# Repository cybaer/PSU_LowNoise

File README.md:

PSU with very low noise (de noiser)

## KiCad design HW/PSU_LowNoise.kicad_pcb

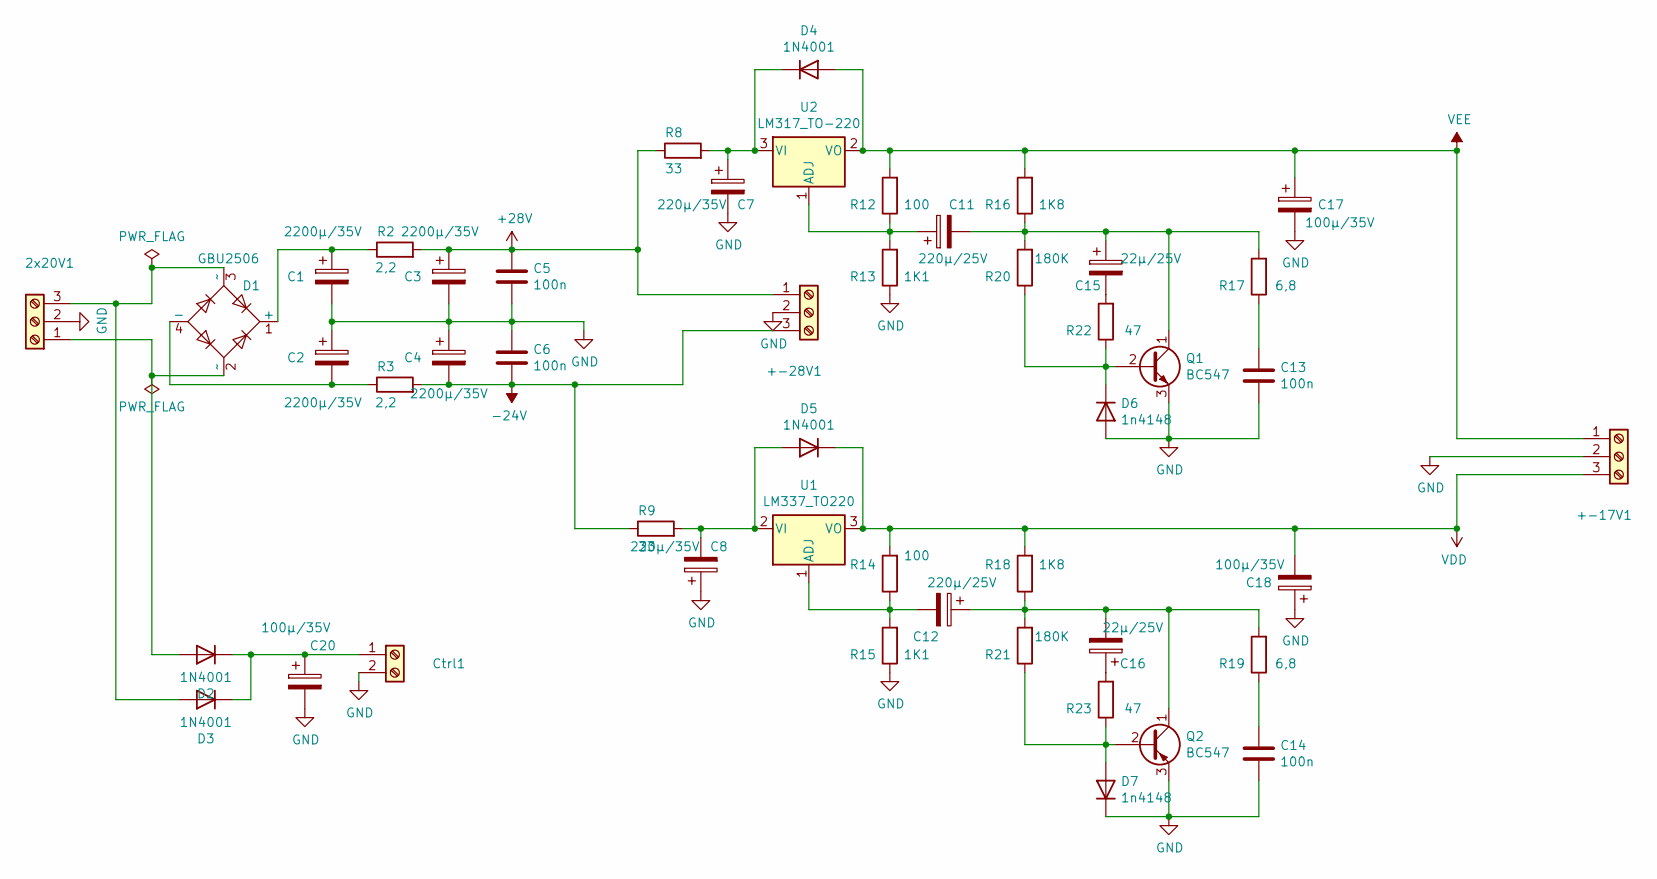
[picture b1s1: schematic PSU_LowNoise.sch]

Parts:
2x20V1: Screw_Terminal_01x03; TerminalBlock_MetzConnect_Type055_RT01503HDWU_1x03_P5.00mm_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
+-17V1, +-28V1: Screw_Terminal_01x03; TerminalBlock_MetzConnect_Type055_RT01503HDWU_1x03_P5.00mm_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
C1, C2, C3, C4: 2200µ/35V; CP_Radial_D12.5mm_P5.00mm
C5, C6, C13, C14: 100n; C_Disc_D3.4mm_W2.1mm_P2.50mm
C7, C8: 220µ/35V; CP_Radial_D8.0mm_P5.00mm
C11, C12: 220µ/25V; CP_Radial_D8.0mm_P5.00mm
C15, C16: 22µ/25V; CP_Radial_D5.0mm_P2.00mm
C17, C18, C20: 100µ/35V; CP_Radial_D8.0mm_P5.00mm
Ctrl1: Screw_Terminal_01x02; TerminalBlock_MetzConnect_Type055_RT01502HDWU_1x02_P5.00mm_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
D1: GBU2506; Diode_Bridge_Vishay_GBU
D2, D3, D4, D5: 1N4001; D_DO-41_SOD81_P10.16mm_Horizontal
D6, D7: 1n4148; D_DO-35_SOD27_P7.62mm_Horizontal
Q1, Q2: BC547; TO-92_Inline
R2, R3: 2,2; R_Axial_DIN0207_L6.3mm_D2.5mm_P7.62mm_Horizontal
R8, R9: 33; R_Axial_DIN0309_L9.0mm_D3.2mm_P12.70mm_Horizontal
R12, R14: 100; R_Axial_DIN0207_L6.3mm_D2.5mm_P7.62mm_Horizontal
R13, R15: 1K1; R_Axial_DIN0207_L6.3mm_D2.5mm_P7.62mm_Horizontal
R16, R18: 1K8; R_Axial_DIN0207_L6.3mm_D2.5mm_P7.62mm_Horizontal
R17, R19: 6,8; R_Axial_DIN0207_L6.3mm_D2.5mm_P7.62mm_Horizontal
R20, R21: 180K; R_Axial_DIN0207_L6.3mm_D2.5mm_P7.62mm_Horizontal
R22, R23: 47; R_Axial_DIN0207_L6.3mm_D2.5mm_P7.62mm_Horizontal
U1: LM337_TO220; TO-220-3_Vertical
U2: LM317_TO-220; TO-220-3_Vertical

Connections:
+28V: +-28V1.1, C3.1, C5.1, R2.2, R8.1
-24V: +-28V1.3, C4.2, C6.2, R3.2, R9.1
GND: 2x20V1.2, +-17V1.2, +-28V1.2, C1.2, C2.1, C3.2, C4.1, C5.2, C6.1, C7.2, C8.1, C13.2, C14.2, C17.2, C18.1, C20.2, Ctrl1.2, D6.2 (A), D7.1 (K), Q1.3 (E), Q2.3 (E), R13.1, R15.1
unnamed: 2x20V1.1, D1.2 (~~), D2.2 (A)
unnamed: 2x20V1.3, D1.3 (~~), D3.2 (A)
unnamed: C1.1, D1.1 (+), R2.1
unnamed: C2.2, D1.4 (-), R3.1
unnamed: C7.1, D4.1 (K), R8.2, U2.3 (VI)
unnamed: C8.2, D5.2 (A), R9.2, U1.2 (VI)
unnamed: C11.1, R12.1, R13.2, U2.1 (ADJ)
unnamed: C11.2, C15.1, Q1.1 (C), R16.1, R17.2, R20.2
unnamed: C12.1, C16.2, Q2.1 (C), R18.1, R19.2, R21.2
unnamed: C12.2, R14.1, R15.2, U1.1 (ADJ)
unnamed: C13.1, R17.1
unnamed: C14.1, R19.1
unnamed: C15.2, R22.2
unnamed: C16.1, R23.2
unnamed: C20.1, Ctrl1.1, D2.1 (K), D3.1 (K)
unnamed: D6.1 (K), Q1.2 (B), R20.1, R22.1
unnamed: D7.2 (A), Q2.2 (B), R21.1, R23.1
VDD: +-17V1.3, C18.2, D5.1 (K), R14.2, R18.2, U1.3 (VO)
VEE: +-17V1.1, C17.1, D4.2 (A), R12.2, R16.2, U2.2 (VO)

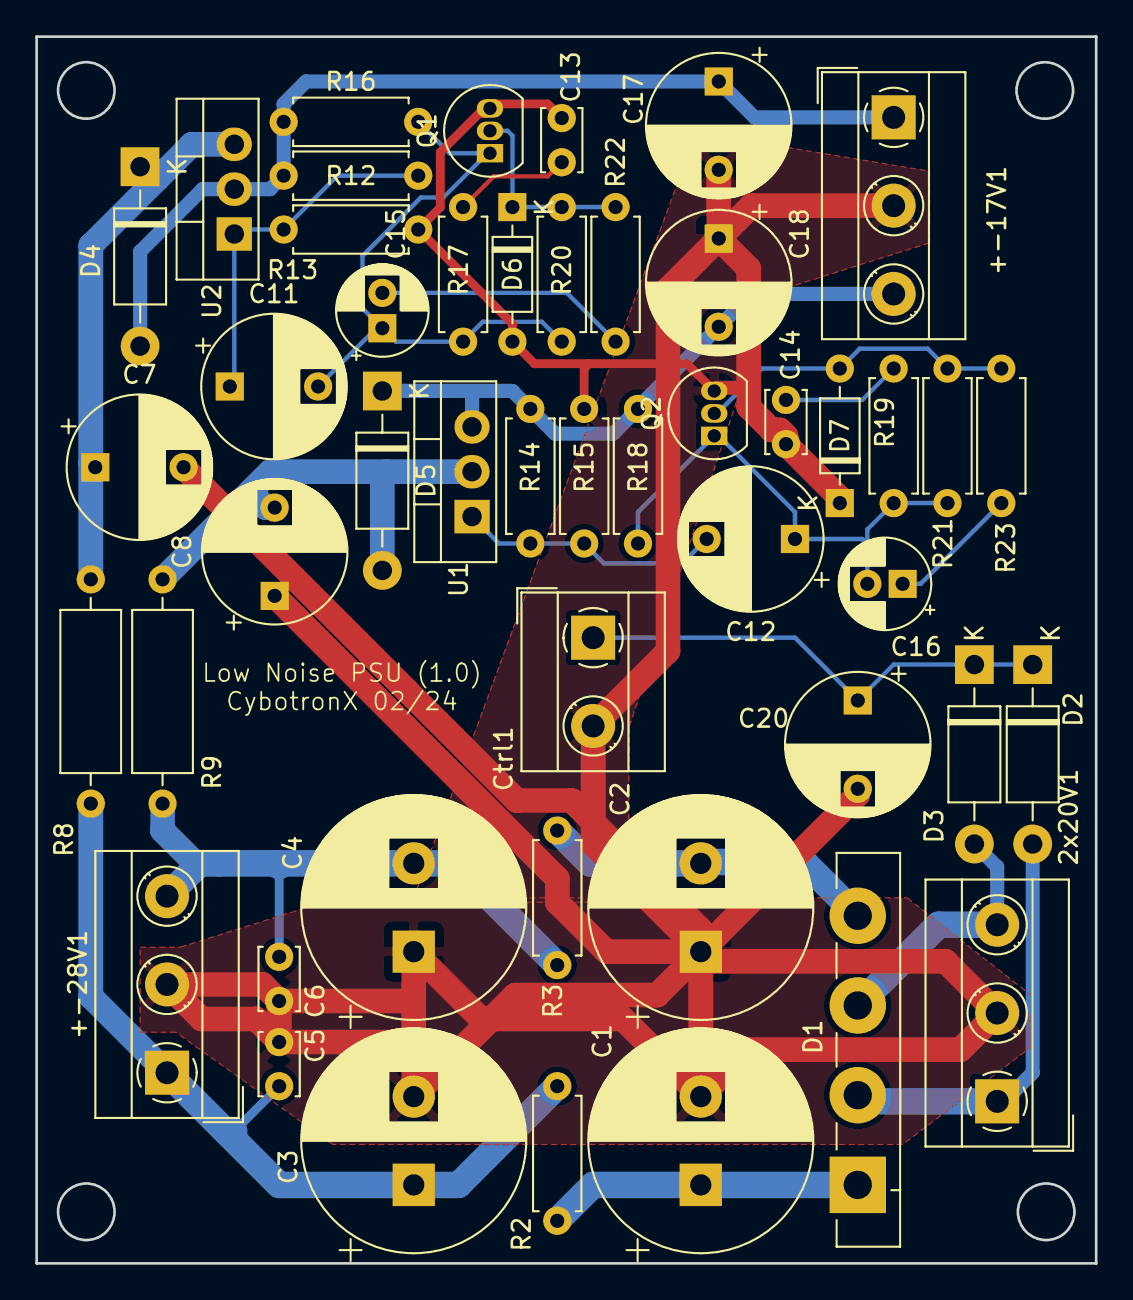
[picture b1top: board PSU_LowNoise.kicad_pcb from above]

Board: 2 copper layers, 60.0 x 69.5 mm, 48 parts (0 on the bottom side), 22 nets.
